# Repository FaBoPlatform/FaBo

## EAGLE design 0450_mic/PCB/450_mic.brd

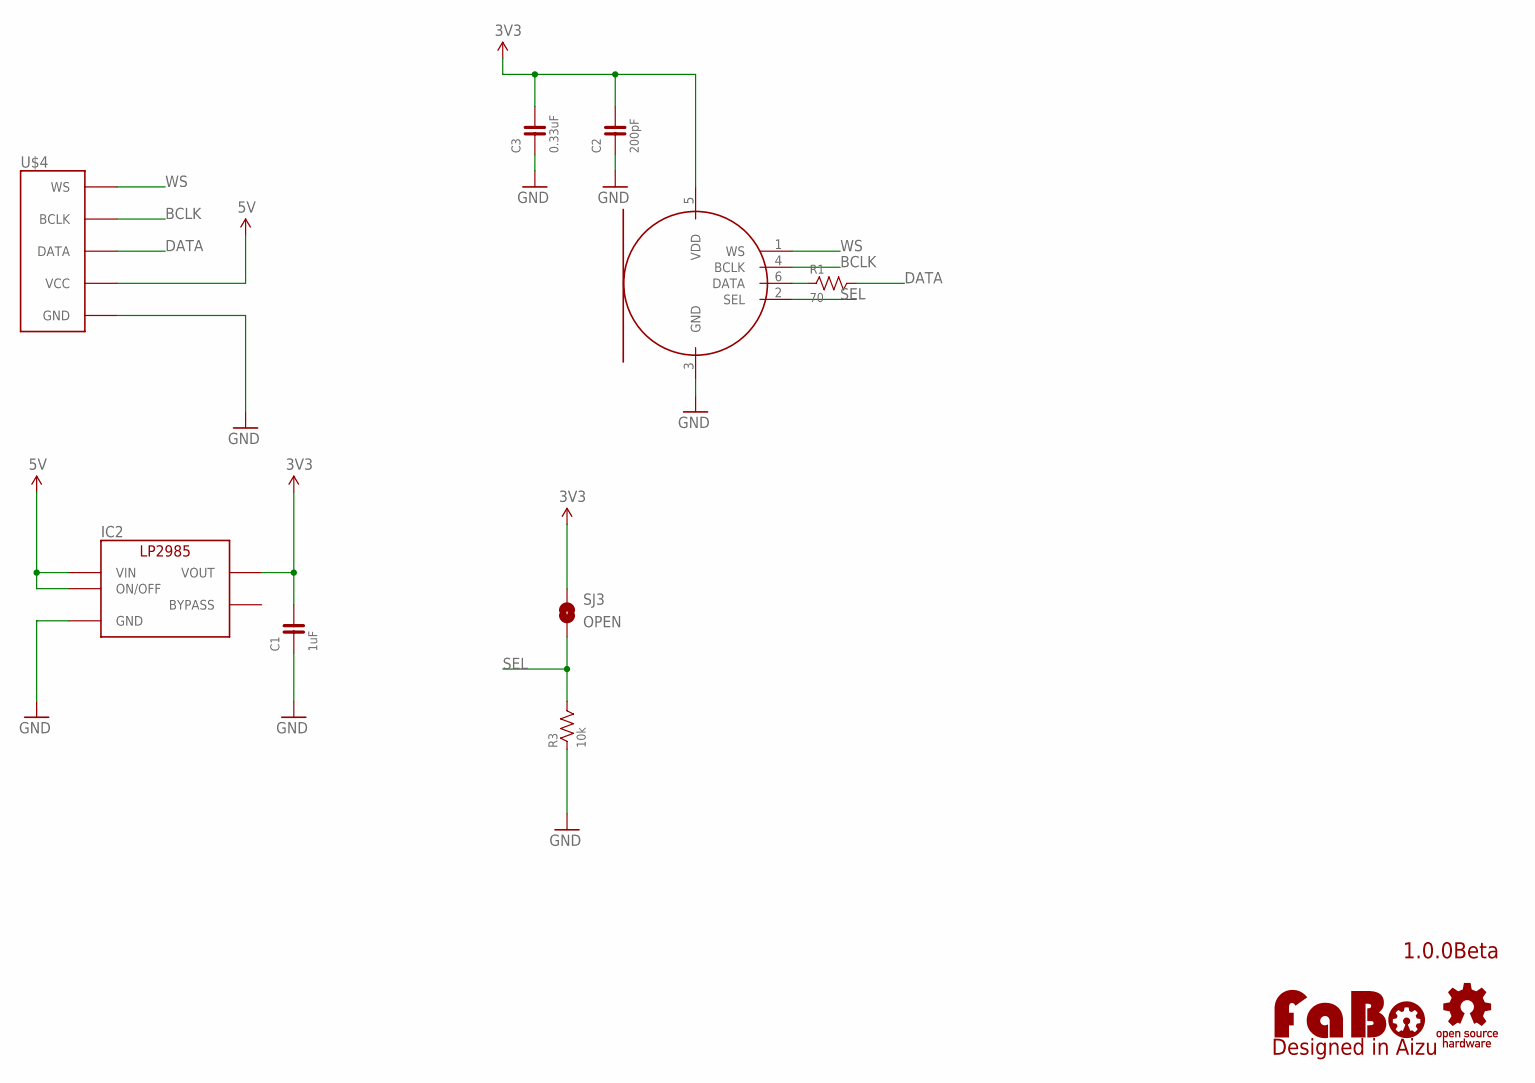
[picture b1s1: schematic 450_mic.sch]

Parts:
C1: 1uF; 0603
C2: 200pF; 0603
C3: 0.33uF; 0603
IC2: LP2985-33DBV; SOT-23-5
LOGO1: LOGO_FABO-M_BOTTOM; LOGO_FABO_M_BOTTOM
MIC1: KW-SPH0645; KNOWLES-SPH0645
R1: 70; 0603
R3: 10k; 0603
SJ3: OPEN; SMD-JUMPER-2-OPEN
U$2: LOGO_OSHW-M_BOTTOM; LOGO_OSHW_M_BOTTOM
U$4: FABO_BRICK_I2S

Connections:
3V3: C1.2, C2.2, C3.2, IC2.5 (VOUT), MIC1.5 (VDD), SJ3.1
5V: IC2.1 (VIN), IC2.3 (ON/OFF), U$4.VCC
BCLK: MIC1.4 (BCLK), U$4.BCLK
DATA: R1.2, U$4.DATA
GND: C1.1, C2.1, C3.1, IC2.2 (GND), MIC1.3 (GND), R3.1, U$4.GND
unnamed: MIC1.6 (DATA), R1.1
SEL: MIC1.2 (SEL), R3.2, SJ3.2
WS: MIC1.1 (WS), U$4.WS

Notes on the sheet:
1.0.0Beta

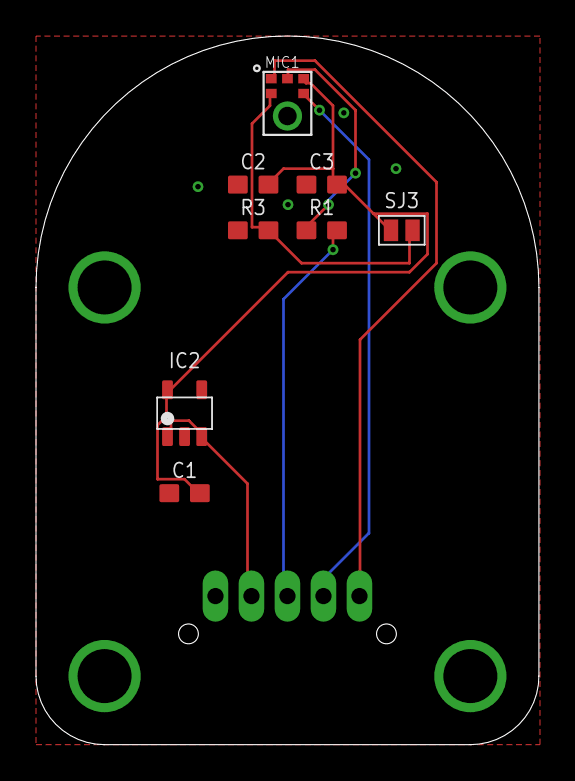
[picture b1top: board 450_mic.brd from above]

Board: 2 copper layers, 27.9 x 39.4 mm, 11 parts (0 on the bottom side), 8 nets.

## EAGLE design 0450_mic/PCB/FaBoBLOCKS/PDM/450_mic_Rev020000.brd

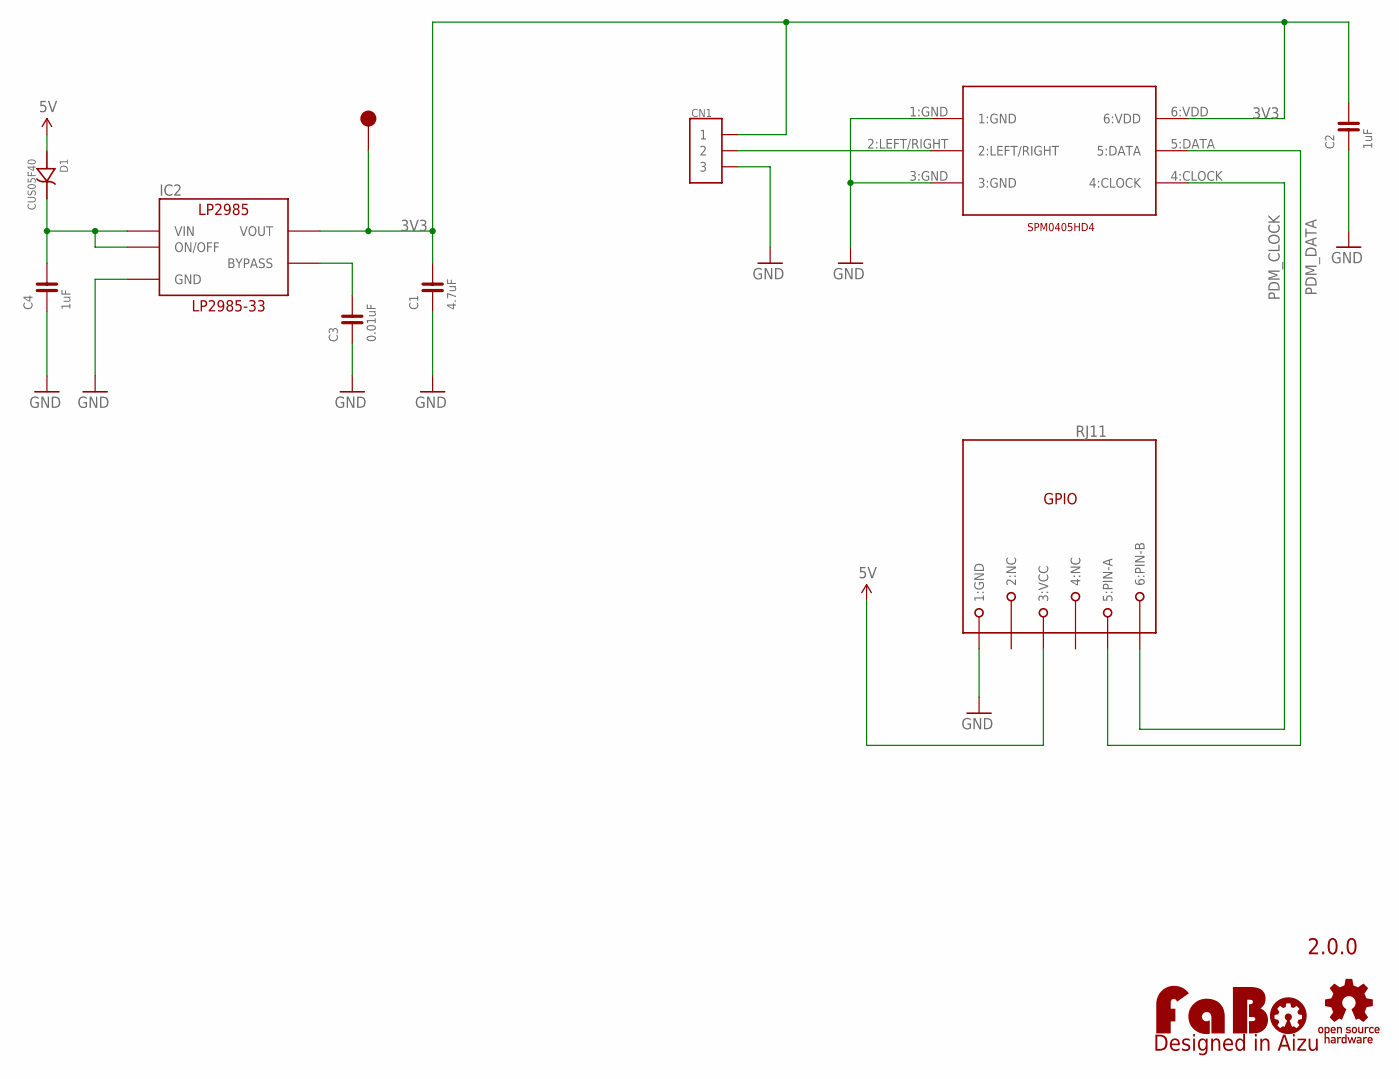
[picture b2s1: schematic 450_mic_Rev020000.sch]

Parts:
C1: 4.7uF; 0603
C2, C4: 1uF; 0603
C3: 0.01uF; 0603
CN1: PIN_1X3
D1: CUS05F40
IC2: LP2985-33DBV; SOT-23-5
LOGO1: LOGO_FABO-M; LOGO_FABO_M
RJ11: MODULAR-JACK-6P-RJ11_GPIO; 7002-6PXC-X
TP3: TP-15
U$2: LOGO_OSHW-M_BOTTOM; LOGO_OSHW_M_BOTTOM
U$5: SPM0405H; SPM4050

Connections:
3V3: C1.2, C2.2, CN1.1, IC2.5 (VOUT), TP3.1, U$5.6:VDD
5V: D1.A (ANODE), RJ11.3 (3:VCC)
GND: C1.1, C2.1, C3.1, C4.1, CN1.3, IC2.2 (GND), RJ11.1 (1:GND), U$5.1:GND, U$5.3:GND
unnamed: C3.2, IC2.4 (BYPASS)
unnamed: C4.2, D1.C (CATHODE), IC2.1 (VIN), IC2.3 (ON/OFF)
unnamed: CN1.2, U$5.2:LEFT/RIGHT
PDM_CLOCK: RJ11.6 (6:PIN-B), U$5.4:CLOCK
PDM_DATA: RJ11.5 (5:PIN-A), U$5.5:DATA

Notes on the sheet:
2.0.0
LP2985-33

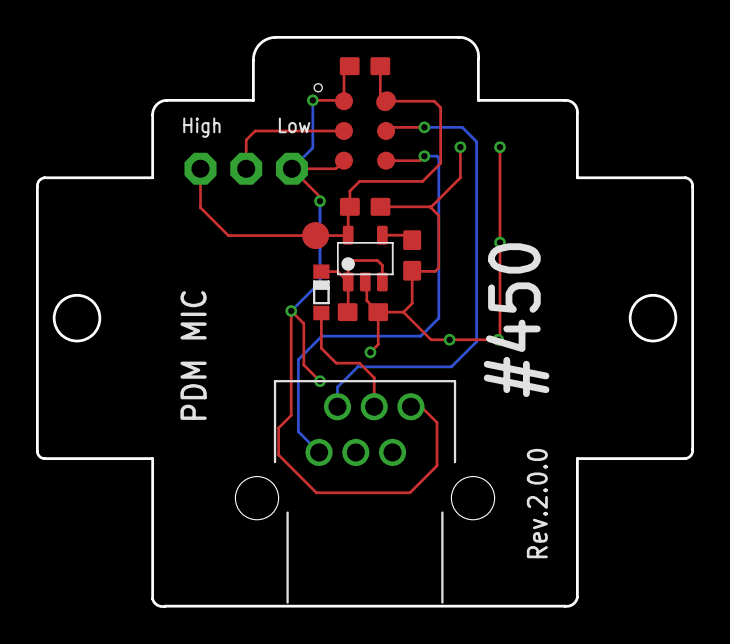
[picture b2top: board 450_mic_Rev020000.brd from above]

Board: 2 copper layers, 36.4 x 31.6 mm, 14 parts (1 on the bottom side), 8 nets.

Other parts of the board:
U$3, U$4: 4-1BLOCK

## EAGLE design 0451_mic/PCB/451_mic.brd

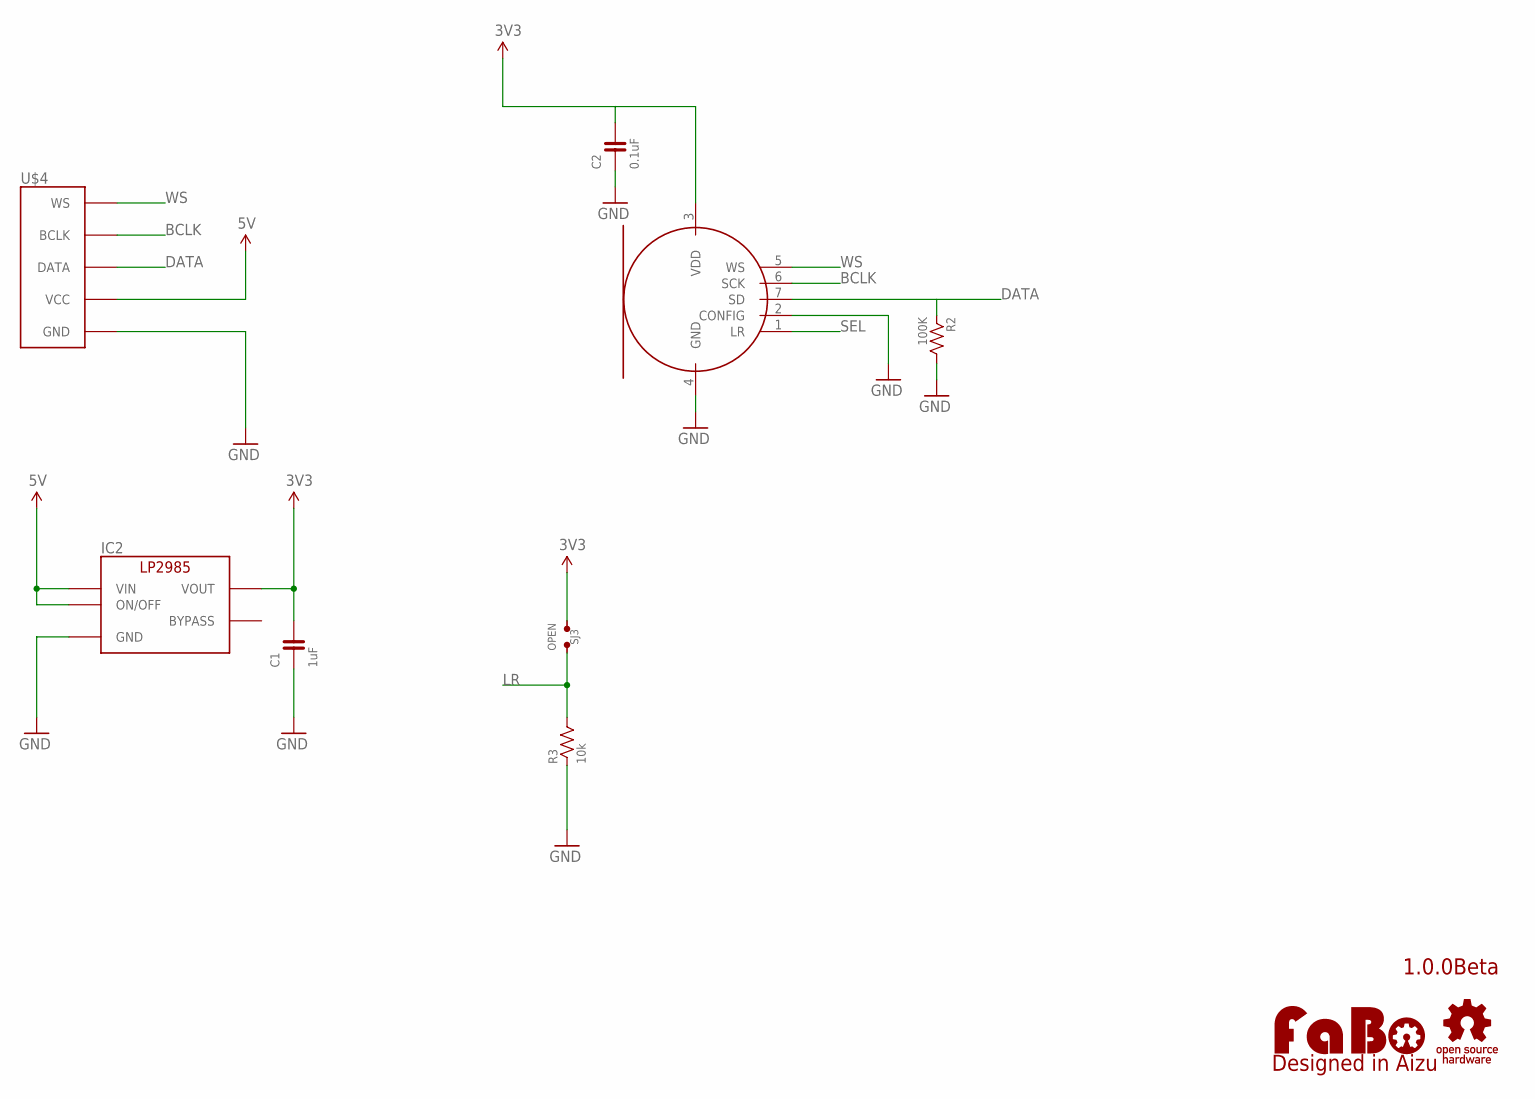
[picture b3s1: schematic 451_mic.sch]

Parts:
C1: 1uF; 0603
C2: 0.1uF; 0603
IC2: LP2985-33DBV; SOT-23-5
LOGO1: LOGO_FABO-M_BOTTOM; LOGO_FABO_M_BOTTOM
MIC: TDK-ICS43432
R2: 100K; 0603
R3: 10k; 0603
SJ3: OPEN; SMD-JUMPER-2-OPEN
U$2: LOGO_OSHW-M_BOTTOM; LOGO_OSHW_M_BOTTOM
U$4: FABO_BRICK_I2S

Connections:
3V3: C1.2, C2.2, IC2.5 (VOUT), MIC.3 (VDD), SJ3.1
5V: IC2.1 (VIN), IC2.3 (ON/OFF), U$4.VCC
BCLK: MIC.6 (SCK), U$4.BCLK
DATA: MIC.7 (SD), R2.1, U$4.DATA
GND: C1.1, C2.1, IC2.2 (GND), MIC.2 (CONFIG), MIC.4 (GND), R2.2, R3.1, U$4.GND
LR: R3.2, SJ3.2
SEL: MIC.1 (LR)
WS: MIC.5 (WS), U$4.WS

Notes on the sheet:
1.0.0Beta

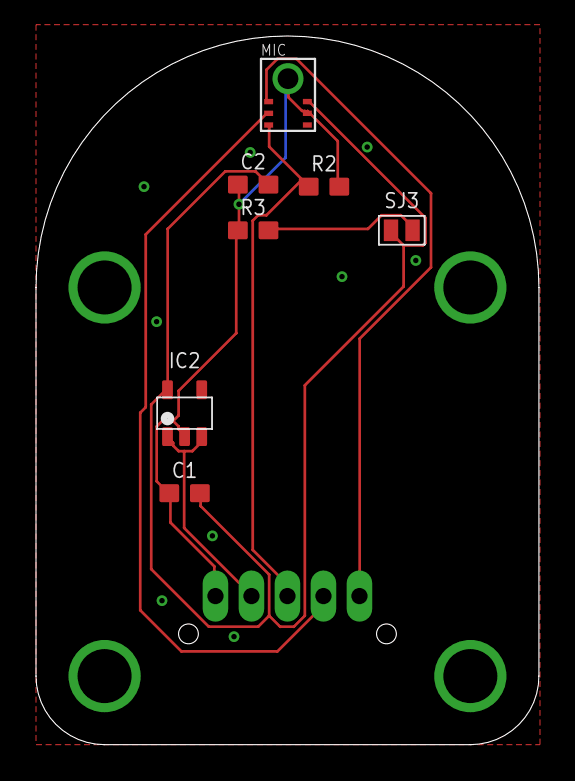
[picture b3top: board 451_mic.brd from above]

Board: 2 copper layers, 27.9 x 39.4 mm, 10 parts (0 on the bottom side), 7 nets.

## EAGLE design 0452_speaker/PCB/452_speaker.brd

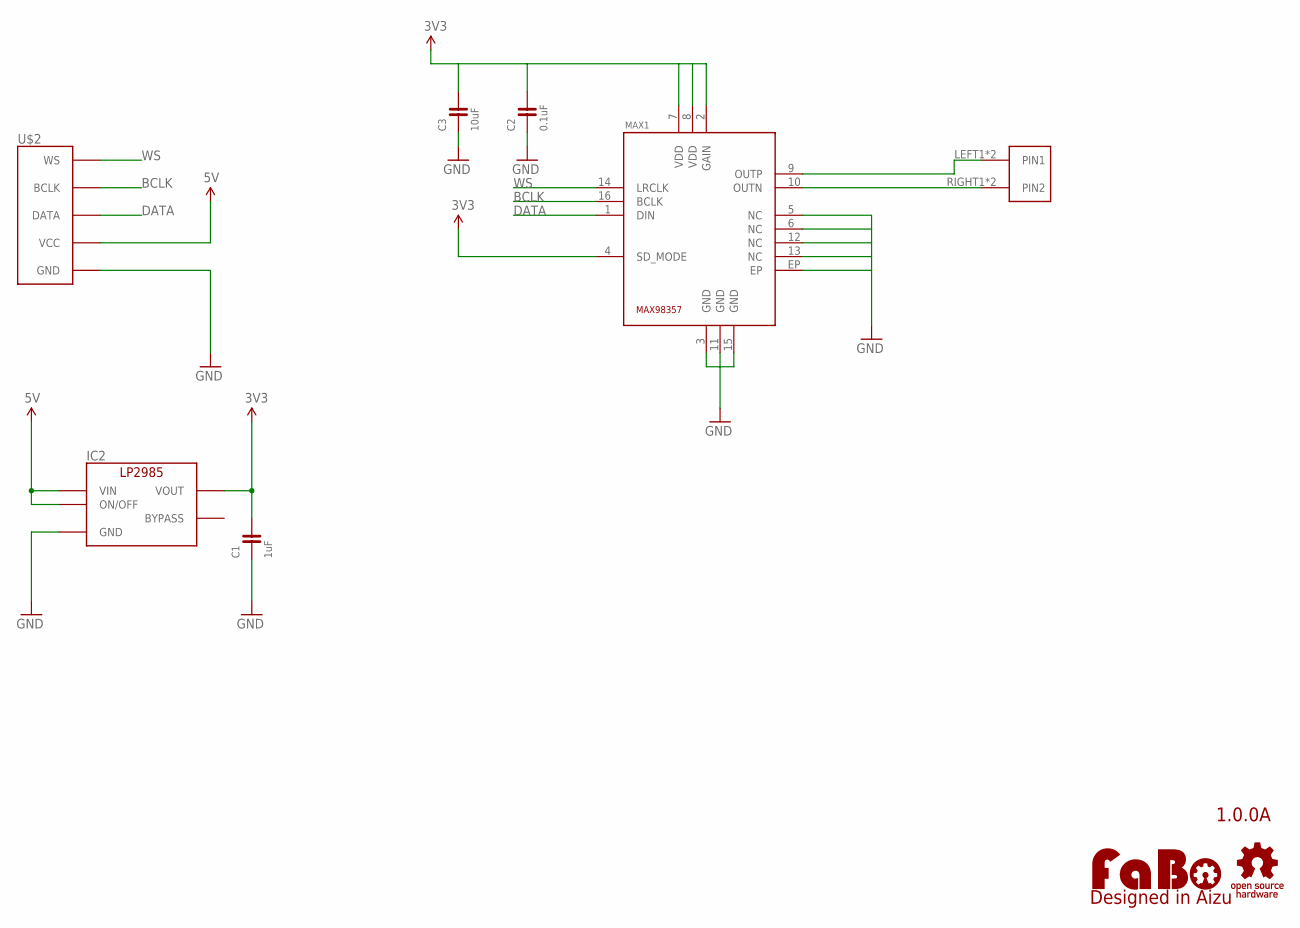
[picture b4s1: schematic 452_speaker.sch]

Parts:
C1: 1uF; 0603
C2: 0.1uF; 0603
C3: 10uF; 0603
IC2: LP2985-33DBV; SOT-23-5
LOGO1: LOGO_FABO-M; LOGO_FABO_M
MAX1: MA-MAX98357; MAXIM-MAX98357
U$2: FABO_BRICK_I2S
U$3: LOGO_OSHW-M_BOTTOM; LOGO_OSHW_M_BOTTOM
U$4: ML-1400-S1

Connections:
3V3: C1.2, C2.2, C3.2, IC2.5 (VOUT), MAX1.2 (GAIN), MAX1.4 (SD_MODE), MAX1.7 (VDD), MAX1.8 (VDD)
5V: IC2.1 (VIN), IC2.3 (ON/OFF), U$2.VCC
BCLK: MAX1.16 (BCLK), U$2.BCLK
DATA: MAX1.1 (DIN), U$2.DATA
GND: C1.1, C2.1, C3.1, IC2.2 (GND), MAX1.3 (GND), MAX1.5 (NC), MAX1.6 (NC), MAX1.11 (GND), MAX1.12 (NC), MAX1.13 (NC), MAX1.15 (GND), MAX1.EP, U$2.GND
unnamed: MAX1.10 (OUTN), U$4.RIGHT1 (PIN2), U$4.RIGHT2 (PIN2)
unnamed: MAX1.9 (OUTP), U$4.LEFT1 (PIN1), U$4.LEFT2 (PIN1)
WS: MAX1.14 (LRCLK), U$2.WS

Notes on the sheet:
1.0.0A

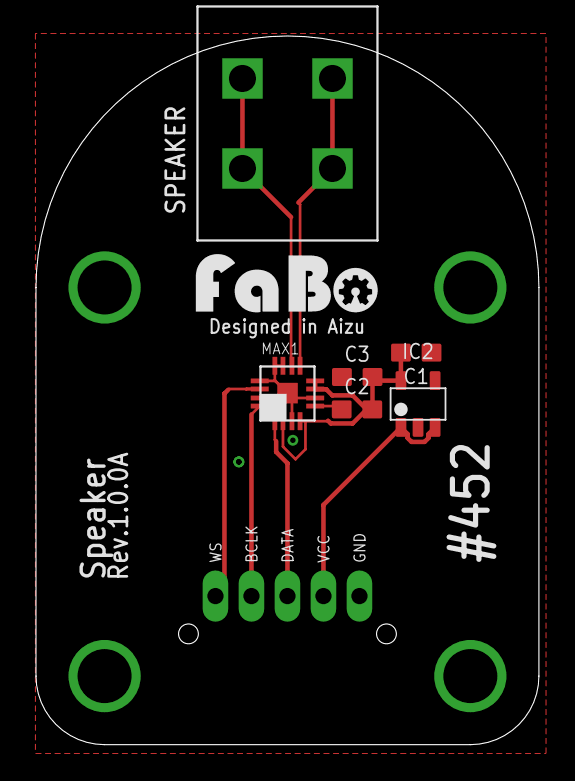
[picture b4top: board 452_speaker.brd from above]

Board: 2 copper layers, 27.9 x 39.4 mm, 9 parts (0 on the bottom side), 8 nets.

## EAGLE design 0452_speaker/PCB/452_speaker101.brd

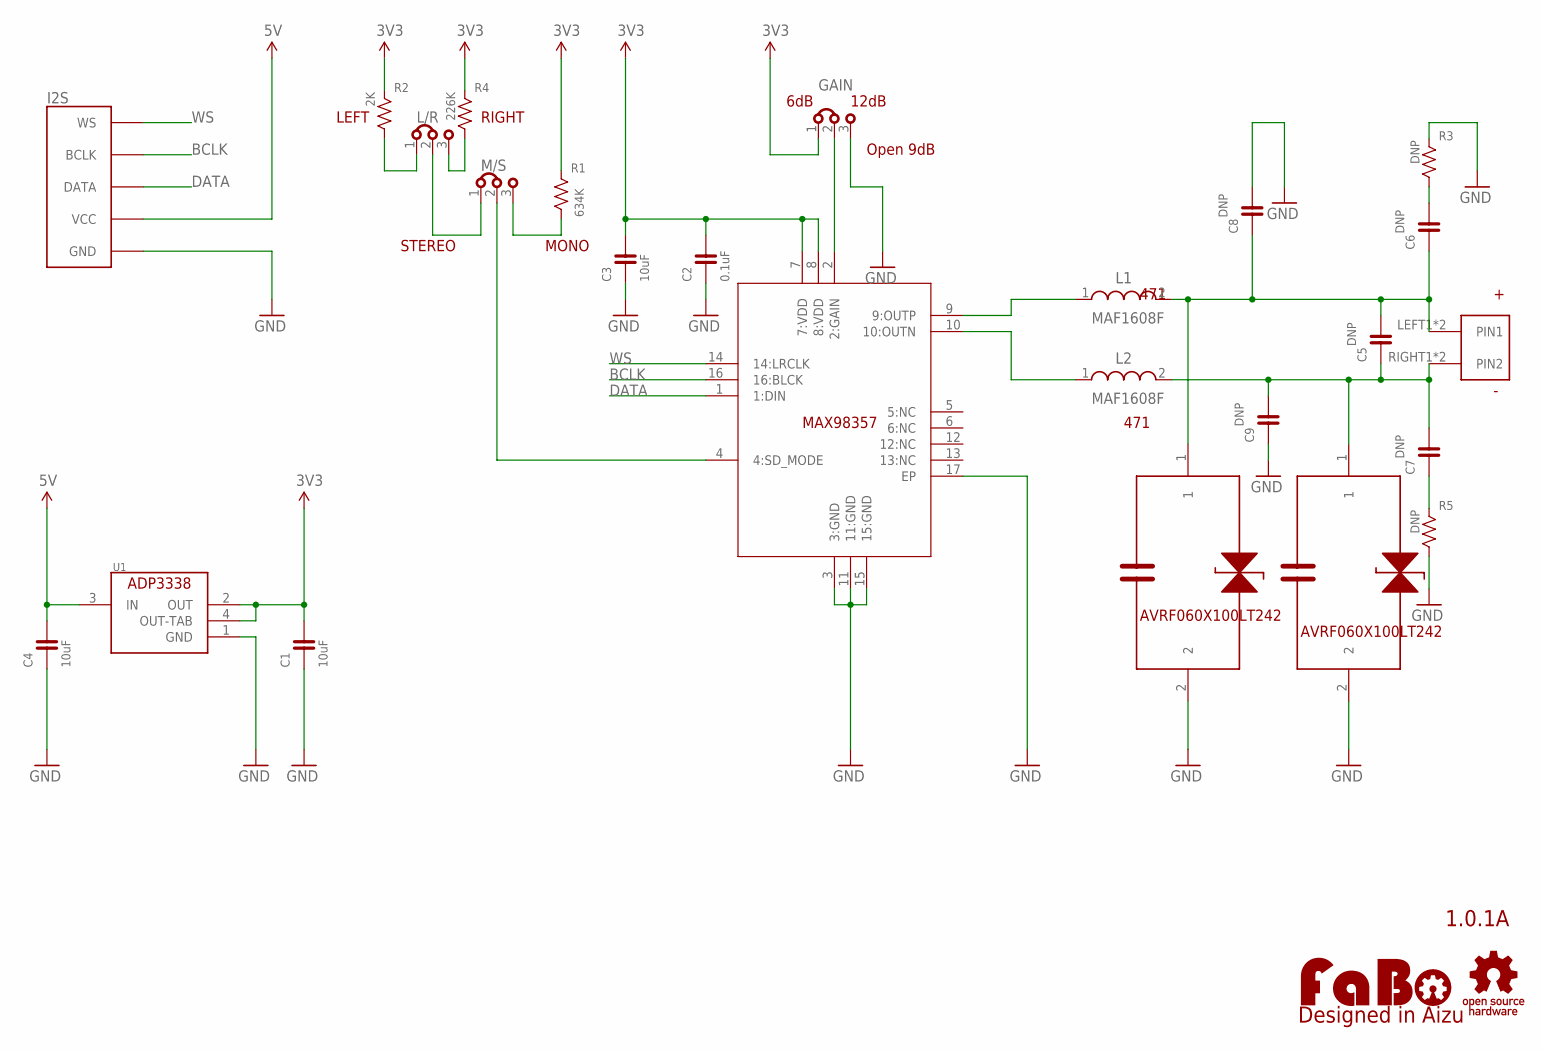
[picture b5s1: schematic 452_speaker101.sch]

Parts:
C1, C3, C4: 10uF; 0603
C2: 0.1uF; 0603
C5, C6, C7, C8, C9: DNP; 0603
GAIN: JUMPERS_JP2-2MM
I2S: FABO_BRICK_I2S
L1, L2: MAF1608F
L/R: JUMPERS_JP2-2MM
LOGO1: LOGO_FABO-M; LOGO_FABO_M
M/S: JUMPERS_JP2-2MM
R1: 634K; 0603
R2: 2K; 0603
R3, R5: DNP; 0603
R4: 226K; 0603
U1: ADP3338AKCZ; SOT-223-KC3
U$2: MAX98357A,B; TQFN(16L3*3*0.75)
U$3: LOGO_OSHW-M_BOTTOM; LOGO_OSHW_M_BOTTOM
U$4: ML-1400-S1
U$5, U$6: AVRF060X100LT242; AVRF0X0X100LT_0603

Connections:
3V3: C1.2, C2.2, C3.2, GAIN.1, R1.1, R2.1, R4.1, U1.2 (OUT), U1.4 (OUT-TAB), U$2.7 (7:VDD), U$2.8 (8:VDD)
5V: C4.2, I2S.VCC, U1.3 (IN)
BCLK: I2S.BCLK, U$2.16 (16:BLCK)
DATA: I2S.DATA, U$2.1 (1:DIN)
GND: C1.1, C2.1, C3.1, C4.1, C8.2, C9.1, GAIN.3, I2S.GND, R3.1, R5.2, U1.1 (GND), U$2.3 (3:GND), U$2.11 (11:GND), U$2.15 (15:GND), U$2.17 (EP), U$5.2, U$6.2
unnamed: L2.1 (3), U$2.10 (10:OUTN)
unnamed: L1.1 (3), U$2.9 (9:OUTP)
unnamed: C5.1, C7.2, C9.2, L2.2 (4), U$4.RIGHT1 (PIN2), U$4.RIGHT2 (PIN2), U$6.1
unnamed: GAIN.2, U$2.2 (2:GAIN)
unnamed: L/R.2, M/S.1
unnamed: M/S.2, U$2.4 (4:SD_MODE)
unnamed: M/S.3, R1.2
unnamed: C5.2, C6.1, C8.1, L1.2 (4), U$4.LEFT1 (PIN1), U$4.LEFT2 (PIN1), U$5.1
unnamed: L/R.1, R2.2
unnamed: L/R.3, R4.2
unnamed: C6.2, R3.2
unnamed: C7.1, R5.1
WS: I2S.WS, U$2.14 (14:LRCLK)

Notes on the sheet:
1.0.1A
471
AVRF060X100LT242
6dB
12dB
Open 9dB
LEFT
RIGHT
MONO
STEREO

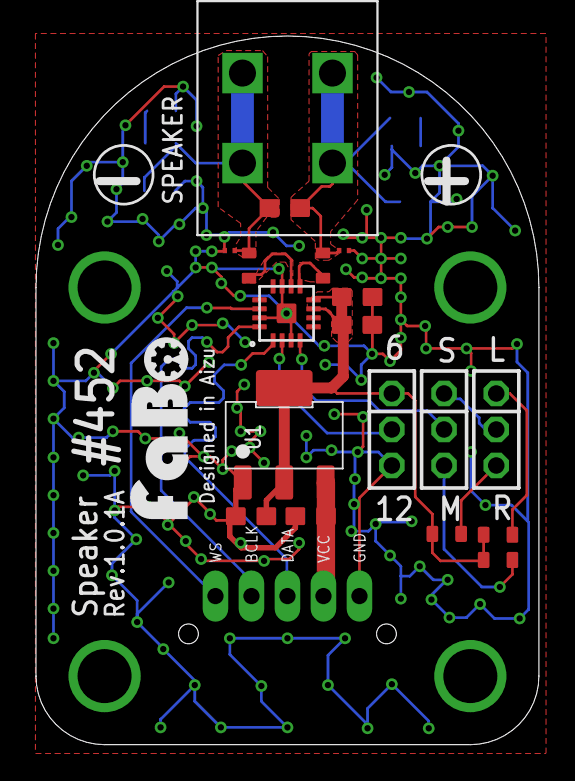
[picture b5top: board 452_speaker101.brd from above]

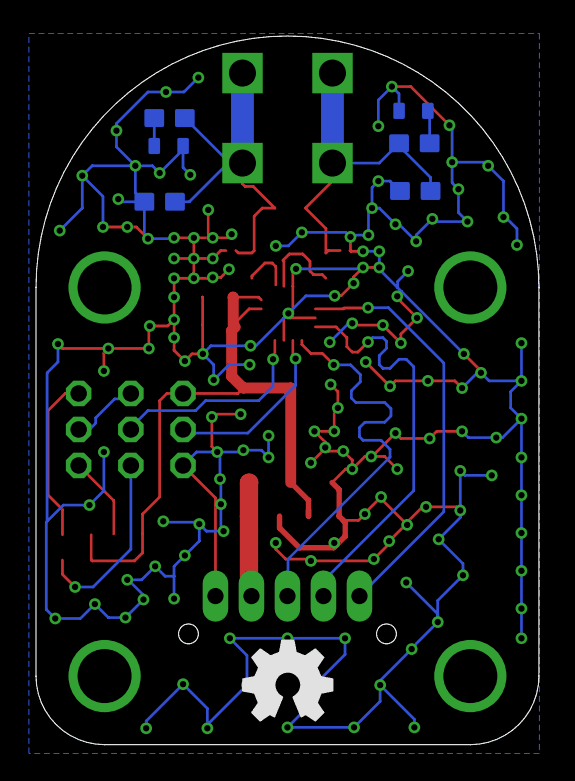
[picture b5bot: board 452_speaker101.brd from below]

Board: 2 copper layers, 27.9 x 39.4 mm, 27 parts (6 on the bottom side), 18 nets.

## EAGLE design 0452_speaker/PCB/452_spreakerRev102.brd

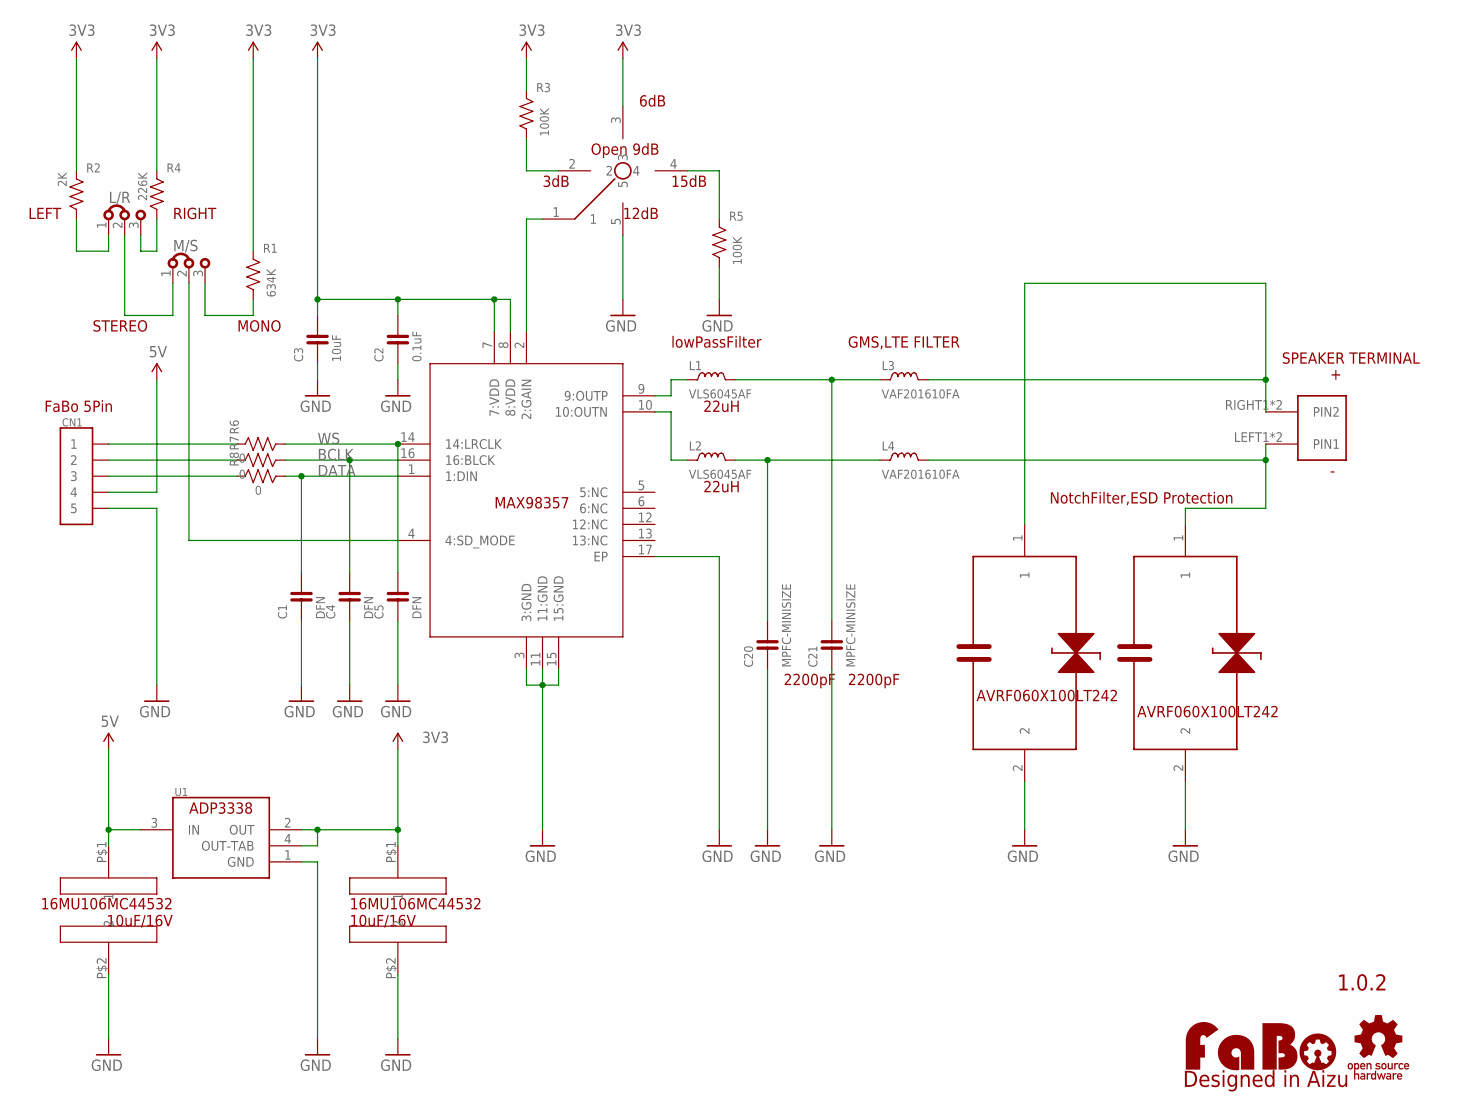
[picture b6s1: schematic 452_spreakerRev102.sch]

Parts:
C1, C4, C5: DFN; 0603
C2: 0.1uF; 0603
C3: 10uF; 0603
C20, C21: MPFC-MINISIZE; DIP-MPFC
C100, C101: POLIYMER_MULTI_LAYER_MU; 4532
CN1: SMD-CONN-5PIN-SM05B-PASS-1; SM05B-PASS-1
L1, L2: VLS6045AF
L3, L4: VAF201610FA; VAF201610FA-1
L/R: JUMPERS_JP2-2MM
LOGO1: LOGO_FABO-M; LOGO_FABO_M
M/S: JUMPERS_JP2-2MM
R1: 634K; 0603
R2: 2K; 0603
R3, R5: 100K; 0603
R4: 226K; 0603
R6, R7, R8: 0; 0603
U1: ADP3338AKCZ; SOT-223-KC3
U$2: MAX98357A,B; TQFN(16L3*3*0.75)
U$3: 2MMJUMPER_CROSS; PINHEAD2MM_CROSS
U$4: ML-1400-S1
U$5, U$6: AVRF060X100LT242; AVRF0X0X100LT_0603
U$10: LOGO_OSHW-M_BOTTOM; LOGO_OSHW_M_BOTTOM

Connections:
3DB: R3.2, U$3.2
3V3: C2.2, C3.2, C101.P$1 (1), R1.1, R2.1, R3.1, R4.1, U1.2 (OUT), U1.4 (OUT-TAB), U$2.7 (7:VDD), U$2.8 (8:VDD), U$3.3
5V: C100.P$1 (1), CN1.4, U1.3 (IN)
15DB: R5.1, U$3.4
BCLK: C4.2, R7.2, U$2.16 (16:BLCK)
DATA: C1.2, R8.2, U$2.1 (1:DIN)
GAIN: U$2.2 (2:GAIN), U$3.1
GND: C1.1, C2.1, C3.1, C4.1, C5.1, C20.1, C21.1, C100.P$2 (2), C101.P$2 (2), CN1.5, R5.2, U1.1 (GND), U$2.3 (3:GND), U$2.11 (11:GND), U$2.15 (15:GND), U$2.17 (EP), U$3.5, U$5.2, U$6.2
LEFT: L/R.1, R2.2
MONO: M/S.3, R1.2
MS: M/S.2, U$2.4 (4:SD_MODE)
unnamed: L2.1, U$2.10 (10:OUTN)
unnamed: L1.1, U$2.9 (9:OUTP)
unnamed: L4.2, U$4.LEFT1 (PIN1), U$4.LEFT2 (PIN1), U$6.1
unnamed: CN1.1, R6.1
unnamed: L3.2, U$4.RIGHT1 (PIN2), U$4.RIGHT2 (PIN2), U$5.1
unnamed: CN1.2, R7.1
unnamed: CN1.3, R8.1
unnamed: C21.2, L1.2, L3.1
unnamed: C20.2, L2.2, L4.1
RIGHT: L/R.3, R4.2
STEREO: L/R.2, M/S.1
WS: C5.2, R6.2, U$2.14 (14:LRCLK)

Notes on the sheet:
1.0.2
22uH
AVRF060X100LT242
6dB
12dB
Open 9dB
LEFT
RIGHT
MONO
STEREO
16MU106MC44532 10uF/16V
FaBo 5Pin
lowPassFilter
NotchFilter,ESD Protection
GMS,LTE FILTER
SPEAKER TERMINAL
2200pF
3dB
15dB

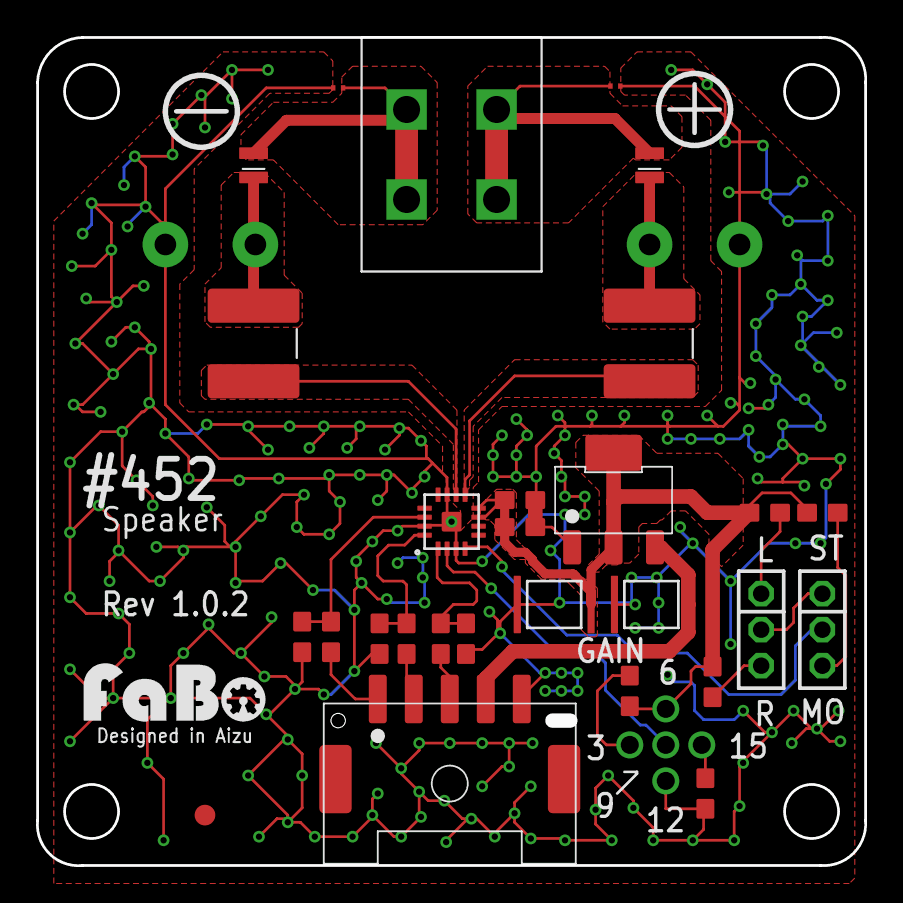
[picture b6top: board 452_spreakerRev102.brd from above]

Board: 2 copper layers, 46.0 x 46.0 mm, 33 parts (0 on the bottom side), 23 nets.

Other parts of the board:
U$12: MARK_POINT_3MM

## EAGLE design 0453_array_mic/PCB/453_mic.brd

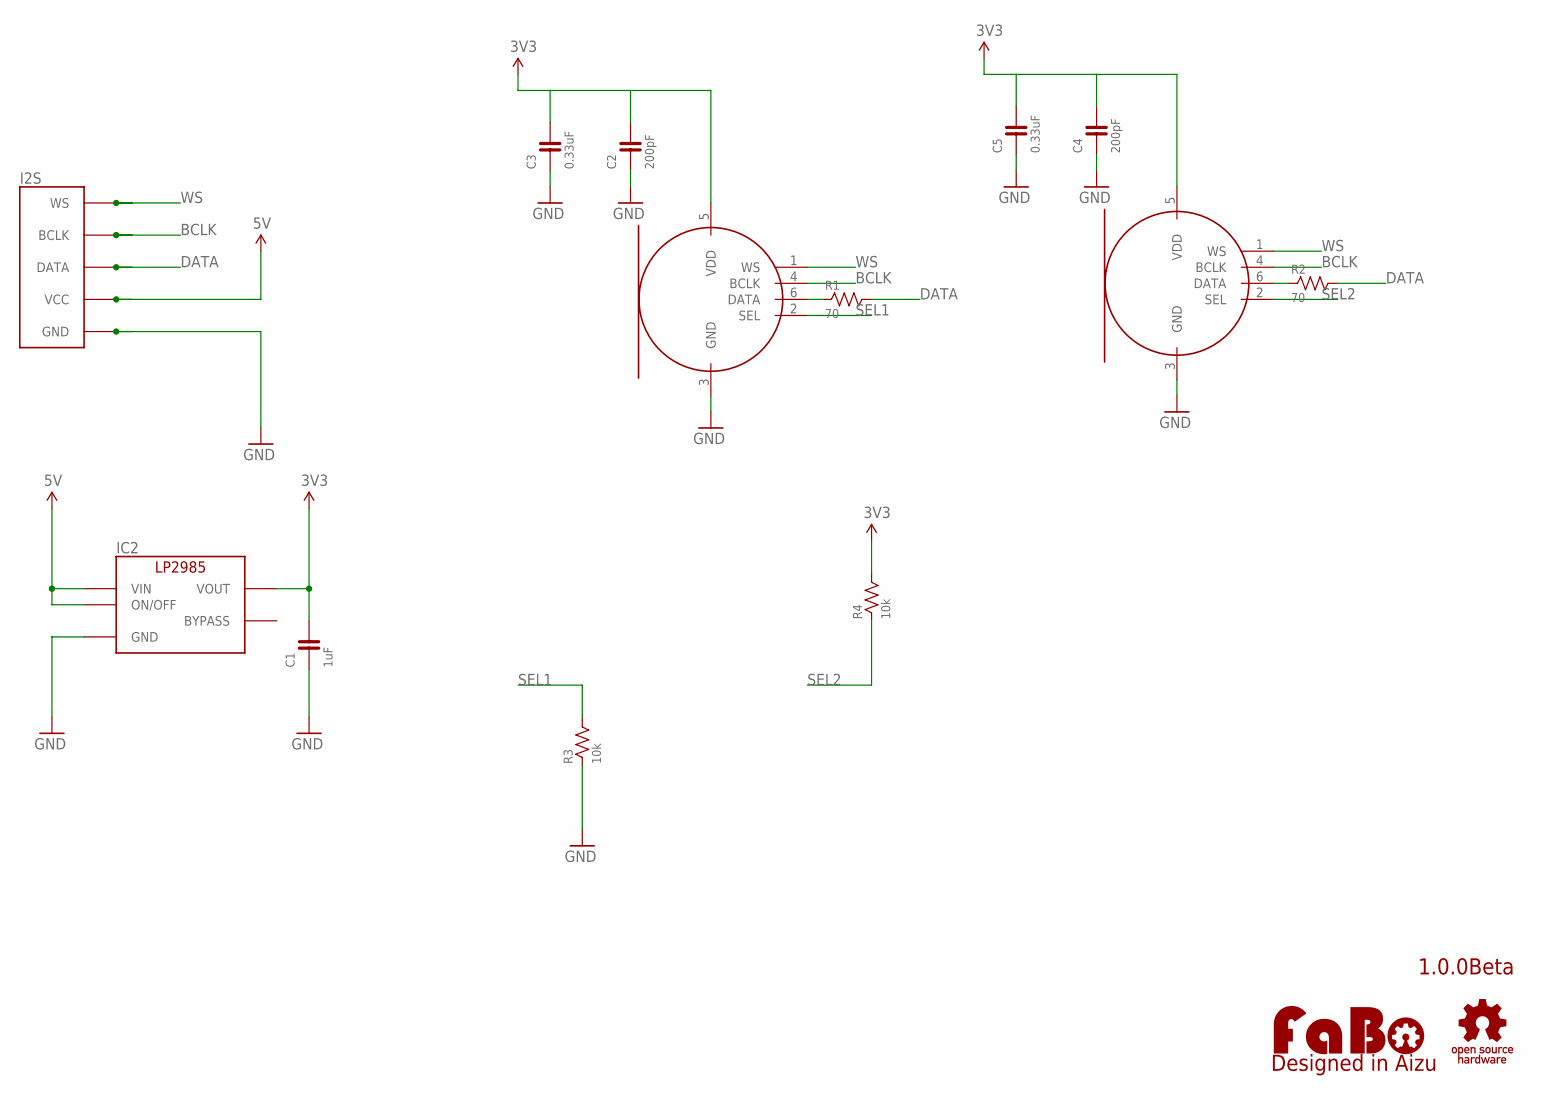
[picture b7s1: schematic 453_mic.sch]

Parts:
C1: 1uF; 0603
C2, C4: 200pF; 0603
C3, C5: 0.33uF; 0603
I2S: FABO_BRICK_I2STOP; FABO_BRICK_I2S_B05B-PARK-1
IC2: LP2985-33DBV; SOT-23-5
LOGO1: LOGO_FABO-M_BOTTOM; LOGO_FABO_M_BOTTOM
MIC1, MIC2: KW-SPH0645; KNOWLES-SPH0645
R1, R2: 70; 0603
R3, R4: 10k; 0603
U$2: LOGO_OSHW-M; LOGO_OSHW_M

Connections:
3V3: C1.2, C2.2, C3.2, C4.2, C5.2, IC2.5 (VOUT), MIC1.5 (VDD), MIC2.5 (VDD), R4.2
5V: I2S.VCC, IC2.1 (VIN), IC2.3 (ON/OFF)
BCLK: I2S.BCLK, MIC1.4 (BCLK), MIC2.4 (BCLK)
DATA: I2S.DATA, R1.2, R2.2
GND: C1.1, C2.1, C3.1, C4.1, C5.1, I2S.GND, IC2.2 (GND), MIC1.3 (GND), MIC2.3 (GND), R3.1
unnamed: MIC2.6 (DATA), R2.1
unnamed: MIC1.6 (DATA), R1.1
SEL1: MIC1.2 (SEL), R3.2
SEL2: MIC2.2 (SEL), R4.1
WS: I2S.WS, MIC1.1 (WS), MIC2.1 (WS)

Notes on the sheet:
1.0.0Beta

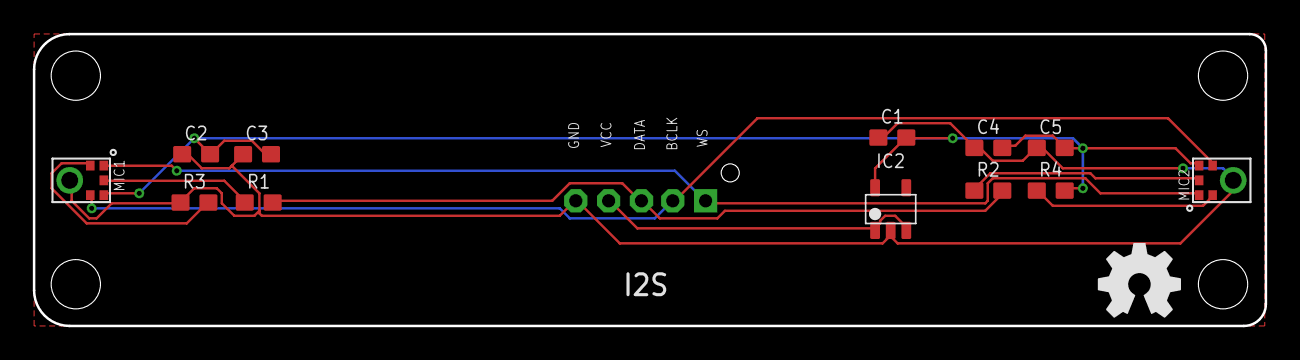
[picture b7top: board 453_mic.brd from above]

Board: 2 copper layers, 75.0 x 17.8 mm, 15 parts (0 on the bottom side), 10 nets.

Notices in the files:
parts and their libraries:
FaBo-Template: Released under the Creative Commons Attribution-ShareAlike 4.0 License
https://creativecommons.org/licenses/by-sa/4.0
FaBo-etc: Released under the Creative Commons
